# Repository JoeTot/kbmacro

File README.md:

# kbmacro
PCB schematic and design for a 14 key macropad.

# Features
- 14 Key layout
- USB Type-C
- Support for one 2.25x key
- Rotary Encoder
- Support for a 0.91 Inch OLED display
- 9x WS2812B leds
- QMK Support

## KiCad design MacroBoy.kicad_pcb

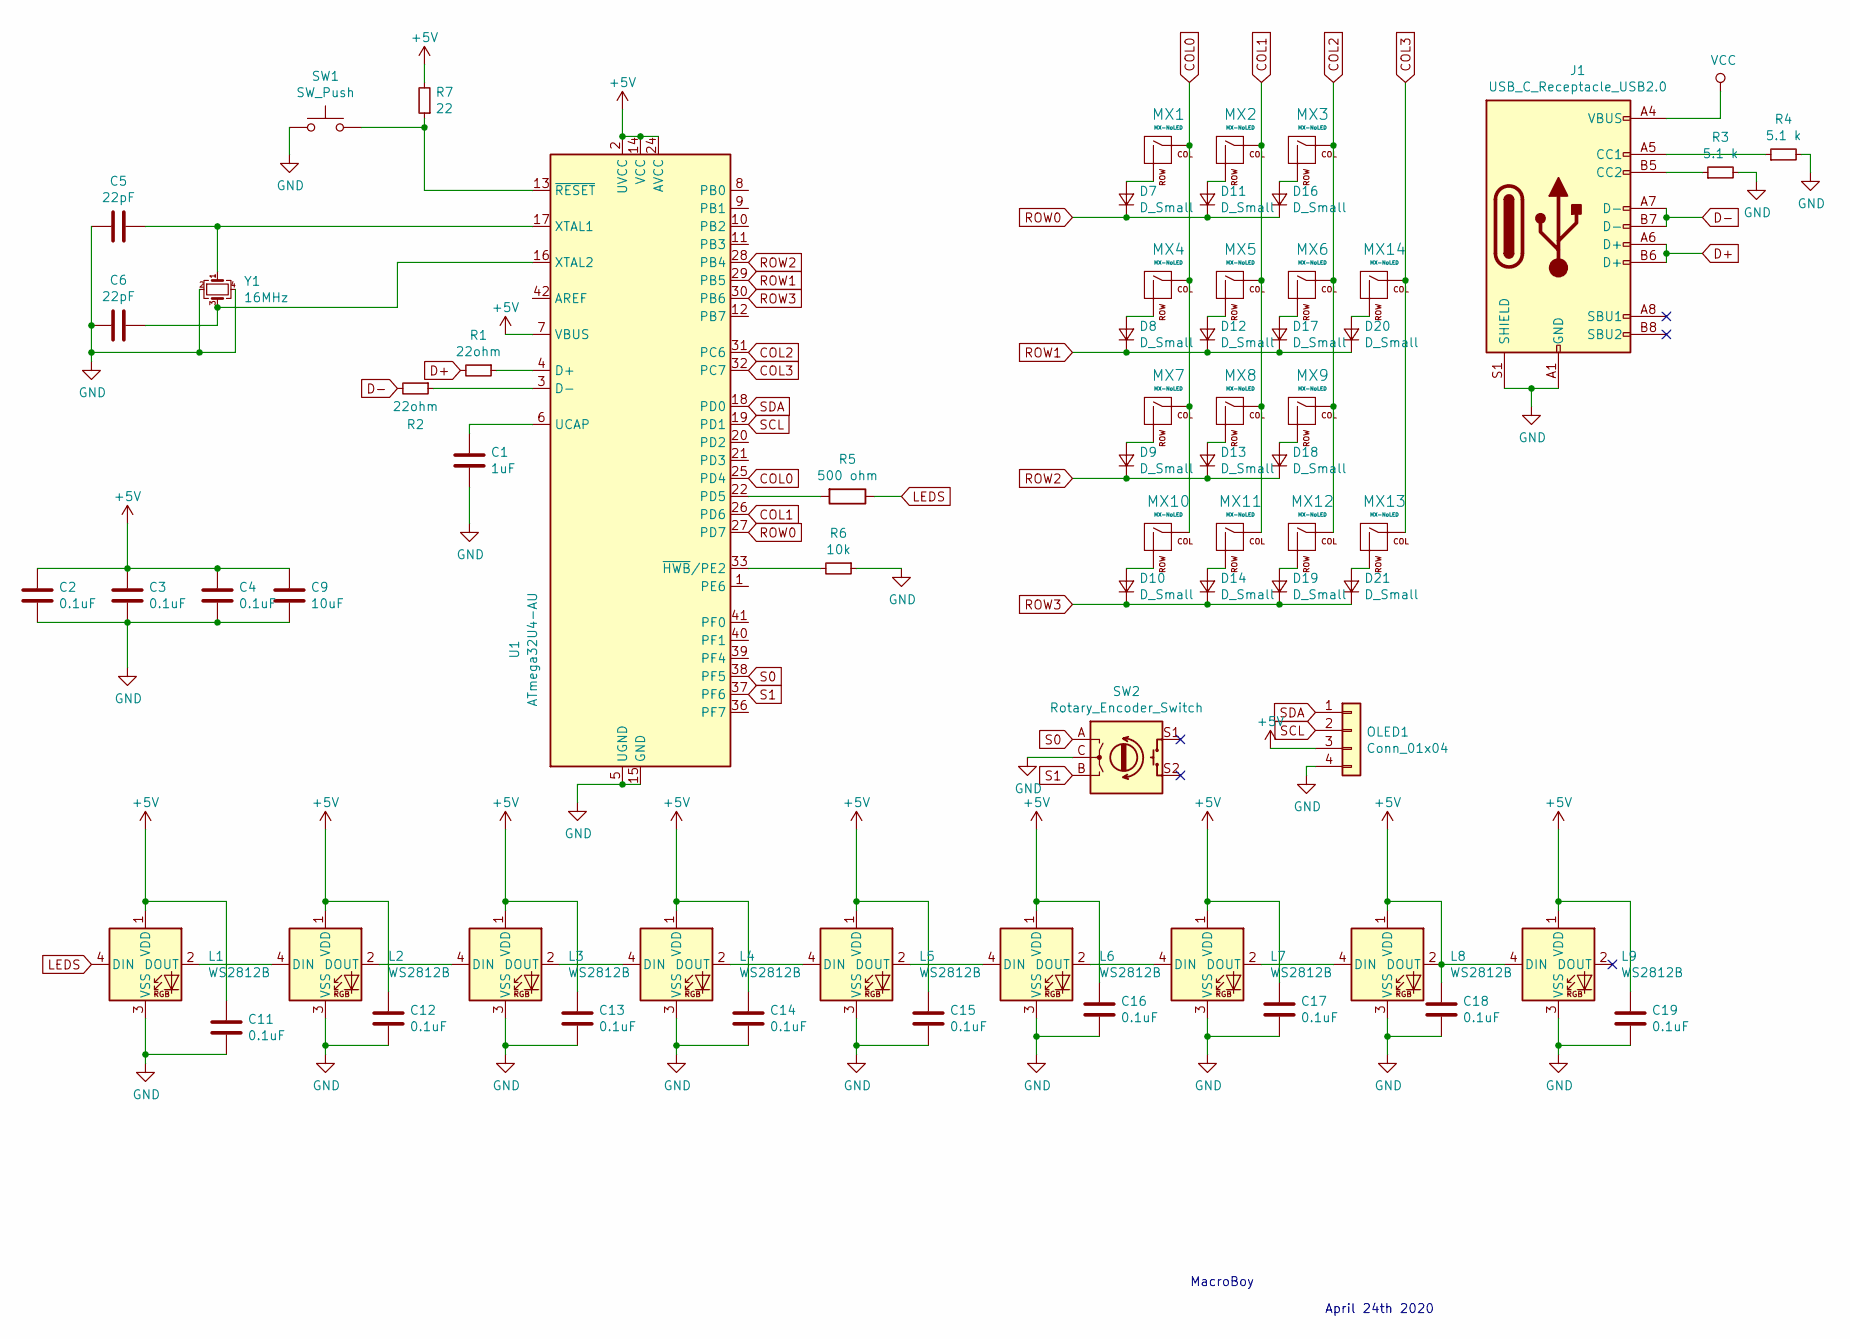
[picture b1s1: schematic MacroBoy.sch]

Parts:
C1: 1uF; C_0805_2012Metric
C2, C3, C4, C11, C12, C13, C14, C15, C16, C17, C18, C19: 0.1uF; C_0805_2012Metric
C5, C6: 22pF; C_0805_2012Metric
C9: 10uF; C_0805_2012Metric
D7, D8, D9, D10, D11, D12, D13, D14, D16, D17, D18, D19, D20, D21: D_Small; D_SOD-123
J1: USB_C_Receptacle_USB2.0; USB_C_Receptacle_HRO_TYPE-C-31-M-12
L1, L2, L3, L4, L5, L6, L7, L8, L9: WS2812B; LED_WS2812B_PLCC4_5.0x5.0mm_P3.2mm
MX1, MX2, MX3, MX4, MX5, MX6, MX7, MX8, MX9, MX10, MX11, MX12, MX14: MX-NoLED; MX-1U-NoLED
MX13: MX-NoLED; MX-2U
OLED1: Conn_01x04; PinHeader_1x04_P2.54mm_Horizontal
R1, R2: 22ohm; R_0805_2012Metric
R3, R4: 5.1 k; R_0805_2012Metric
R5: 500 ohm; R_0805_2012Metric
R6: 10k; R_0805_2012Metric
R7: 22; R_0805_2012Metric
SW1: SW_Push; SKQG-1155865
SW2: Rotary_Encoder_Switch; RotaryEncoder_Alps_EC11E-Switch_Vertical_H20mm
U1: ATmega32U4-AU; TQFP-44_10x10mm_P0.8mm
Y1: 16MHz; Crystal_SMD_3225-4Pin_3.2x2.5mm

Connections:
+5V: C2.1, C3.1, C4.1, C9.1, C11.1, C12.1, C13.1, C14.1, C15.1, C16.1, C17.1, C18.1, C19.1, L1.1 (VDD), L2.1 (VDD), L3.1 (VDD), L4.1 (VDD), L5.1 (VDD), L6.1 (VDD), L7.1 (VDD), L8.1 (VDD), L8.2 (DOUT), L9.1 (VDD), L9.4 (DIN), OLED1.3, R7.2, U1.2 (UVCC), U1.7 (VBUS), U1.14 (VCC), U1.24 (AVCC), U1.34 (VCC), U1.44 (AVCC); also elsewhere on the board
COL0: MX1.1 (COL), MX4.1 (COL), MX7.1 (COL), MX10.1 (COL), U1.25 (PD4)
COL1: MX2.1 (COL), MX5.1 (COL), MX8.1 (COL), MX11.1 (COL), U1.26 (PD6)
COL2: MX3.1 (COL), MX6.1 (COL), MX9.1 (COL), MX12.1 (COL), U1.31 (PC6)
COL3: MX13.1 (COL), MX14.1 (COL), U1.32 (PC7)
D+: J1.A6 (D+), J1.B6 (D+), R1.2
D-: J1.A7 (D-), J1.B7 (D-), R2.2
GND: C1.2, C2.2, C3.2, C4.2, C5.2, C6.2, C9.2, C11.2, C12.2, C13.2, C14.2, C15.2, C16.2, C17.2, C18.2, C19.2, J1.A1 (GND), J1.A12 (GND), J1.B1 (GND), J1.B12 (GND), J1.S1 (SHIELD), L1.3 (VSS), L2.3 (VSS), L3.3 (VSS), L4.3 (VSS), L5.3 (VSS), L6.3 (VSS), L7.3 (VSS), L8.3 (VSS), L9.3 (VSS), OLED1.4, R3.2, R4.2, R6.1, SW1.1, SW2.C, U1.5 (UGND), U1.15 (GND), U1.23 (GND), U1.35 (GND), U1.43 (GND), Y1.2, Y1.4
LEDS: L1.4 (DIN), R5.1
unnamed: C1.1, U1.6 (UCAP)
unnamed: C5.1, U1.17 (XTAL1), Y1.1
unnamed: C6.1, U1.16 (XTAL2), Y1.3
unnamed: D7.2 (A), MX1.2 (ROW)
unnamed: D8.2 (A), MX4.2 (ROW)
unnamed: D9.2 (A), MX7.2 (ROW)
unnamed: D10.2 (A), MX10.2 (ROW)
unnamed: D11.2 (A), MX2.2 (ROW)
unnamed: D12.2 (A), MX5.2 (ROW)
unnamed: D13.2 (A), MX8.2 (ROW)
unnamed: D14.2 (A), MX11.2 (ROW)
unnamed: D16.2 (A), MX3.2 (ROW)
unnamed: D17.2 (A), MX6.2 (ROW)
unnamed: D18.2 (A), MX9.2 (ROW)
unnamed: D19.2 (A), MX12.2 (ROW)
unnamed: D20.2 (A), MX14.2 (ROW)
unnamed: D21.2 (A), MX13.2 (ROW)
unnamed: J1.A5 (CC1), R4.1
unnamed: J1.B5 (CC2), R3.1
unnamed: L1.2 (DOUT), L2.4 (DIN)
unnamed: L2.2 (DOUT), L3.4 (DIN)
unnamed: L3.2 (DOUT), L4.4 (DIN)
unnamed: L4.2 (DOUT), L5.4 (DIN)
unnamed: L5.2 (DOUT), L6.4 (DIN)
unnamed: L6.2 (DOUT), L7.4 (DIN)
unnamed: L7.2 (DOUT), L8.4 (DIN)
unnamed: R1.1, U1.4 (D+)
unnamed: R2.1, U1.3 (D-)
unnamed: R5.2, U1.22 (PD5)
unnamed: R6.2, U1.33 (~HWB~/PE2)
unnamed: R7.1, SW1.2, U1.13 (~RESET)
ROW0: D7.1 (K), D11.1 (K), D16.1 (K), U1.27 (PD7)
ROW1: D8.1 (K), D12.1 (K), D17.1 (K), D20.1 (K), U1.29 (PB5)
ROW2: D9.1 (K), D13.1 (K), D18.1 (K), U1.28 (PB4)
ROW3: D10.1 (K), D14.1 (K), D19.1 (K), D21.1 (K), U1.30 (PB6)
S0: SW2.A, U1.38 (PF5)
S1: SW2.B, U1.37 (PF6)
SCL: OLED1.2, U1.19 (PD1)
SDA: OLED1.1, U1.18 (PD0)
VCC: J1.A4 (VBUS), J1.A9 (VBUS), J1.B4 (VBUS), J1.B9 (VBUS); also elsewhere on the board

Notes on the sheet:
MacroBoy
April 24th 2020

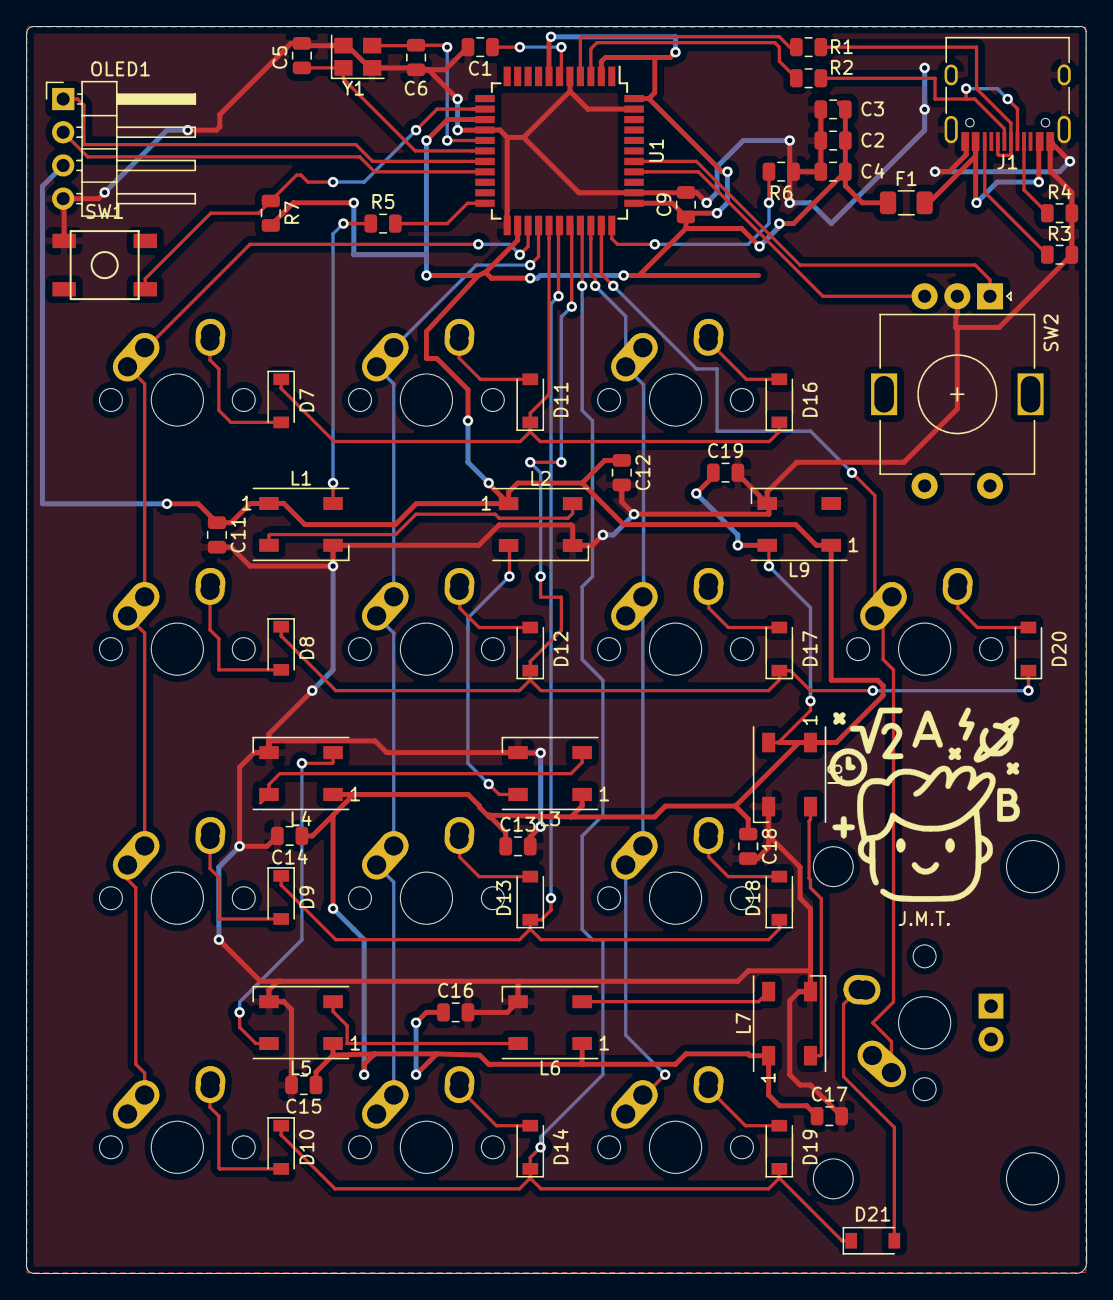
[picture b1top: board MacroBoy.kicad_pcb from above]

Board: 2 copper layers, 81.1 x 95.4 mm, 67 parts (0 on the bottom side), 49 nets.

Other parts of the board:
F1: Polyfuse; Fuse_1206_3216Metric

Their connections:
+5V: F1.1; also elsewhere on the board
VCC: F1.2; also elsewhere on the board

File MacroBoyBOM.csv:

"Id";"Designator";"Package";"Quantity";"Designation";"Supplier and ref";
1;"G***";"logo875";1;"LOGO";;;
2;"C19,C17,C16,C15,C14,C13,C12,C11,C18,C4,C3,C2";"C_0805_2012Metric";12;"0.1uF";;;
3;"MX7,MX1,MX14,MX12,MX11,MX10,MX9,MX8,MX6,MX5,MX4,MX3,MX2";"MX-1U-NoLED";13;"MX-NoLED";;;
4;"SW1";"SKQG-1155865";1;"SW_Push";;;
5;"U1";"TQFP-44_10x10mm_P0.8mm";1;"ATmega32U4-AU";;;
6;"C9";"C_0805_2012Metric";1;"10uF";;;
7;"J1";"USB_C_Receptacle_HRO_TYPE-C-31-M-12";1;"USB_C_Receptacle_USB2.0";;;
8;"R3,R4";"R_0805_2012Metric";2;"5.1 k";;;
9;"Y1";"Crystal_SMD_3225-4Pin_3.2x2.5mm";1;"16MHz";;;
10;"SW2";"RotaryEncoder_Alps_EC11E-Switch_Vertical_H20mm";1;"Rotary_Encoder_Switch";;;
11;"R7,R2,R1";"R_0805_2012Metric";3;"22";;;
12;"R6";"R_0805_2012Metric";1;"10k";;;
13;"R5";"R_0805_2012Metric";1;"500 ohm";;;
14;"OLED1";"PinHeader_1x04_P2.54mm_Horizontal";1;"Conn_01x04";;;
15;"MX13";"MX-2U";1;"MX-NoLED";;;
16;"L9,L8,L7,L6,L5,L4,L3,L2,L1";"LED_WS2812B_PLCC4_5.0x5.0mm_P3.2mm";9;"WS2812B";;;
17;"F1";"Fuse_1206_3216Metric";1;"Polyfuse";;;
18;"D21,D20,D19,D18,D17,D16,D14,D13,D12,D11,D10,D9,D8,D7";"D_SOD-123";14;"D_Small";;;
19;"C6,C5";"C_0805_2012Metric";2;"22pF";;;
20;"C1";"C_0805_2012Metric";1;"1uF";;;
